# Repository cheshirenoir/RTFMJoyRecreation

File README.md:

# RTFMJoyRecreation
A recreation of the classic Acorn Archimedes joystick adaptor for use in the EcoNet module socket.
Redeveloped by the StarDot Community, including Cheshirenoir, IanJeffray, IanS, Dazzathedazza and others.
This version CC BY SA

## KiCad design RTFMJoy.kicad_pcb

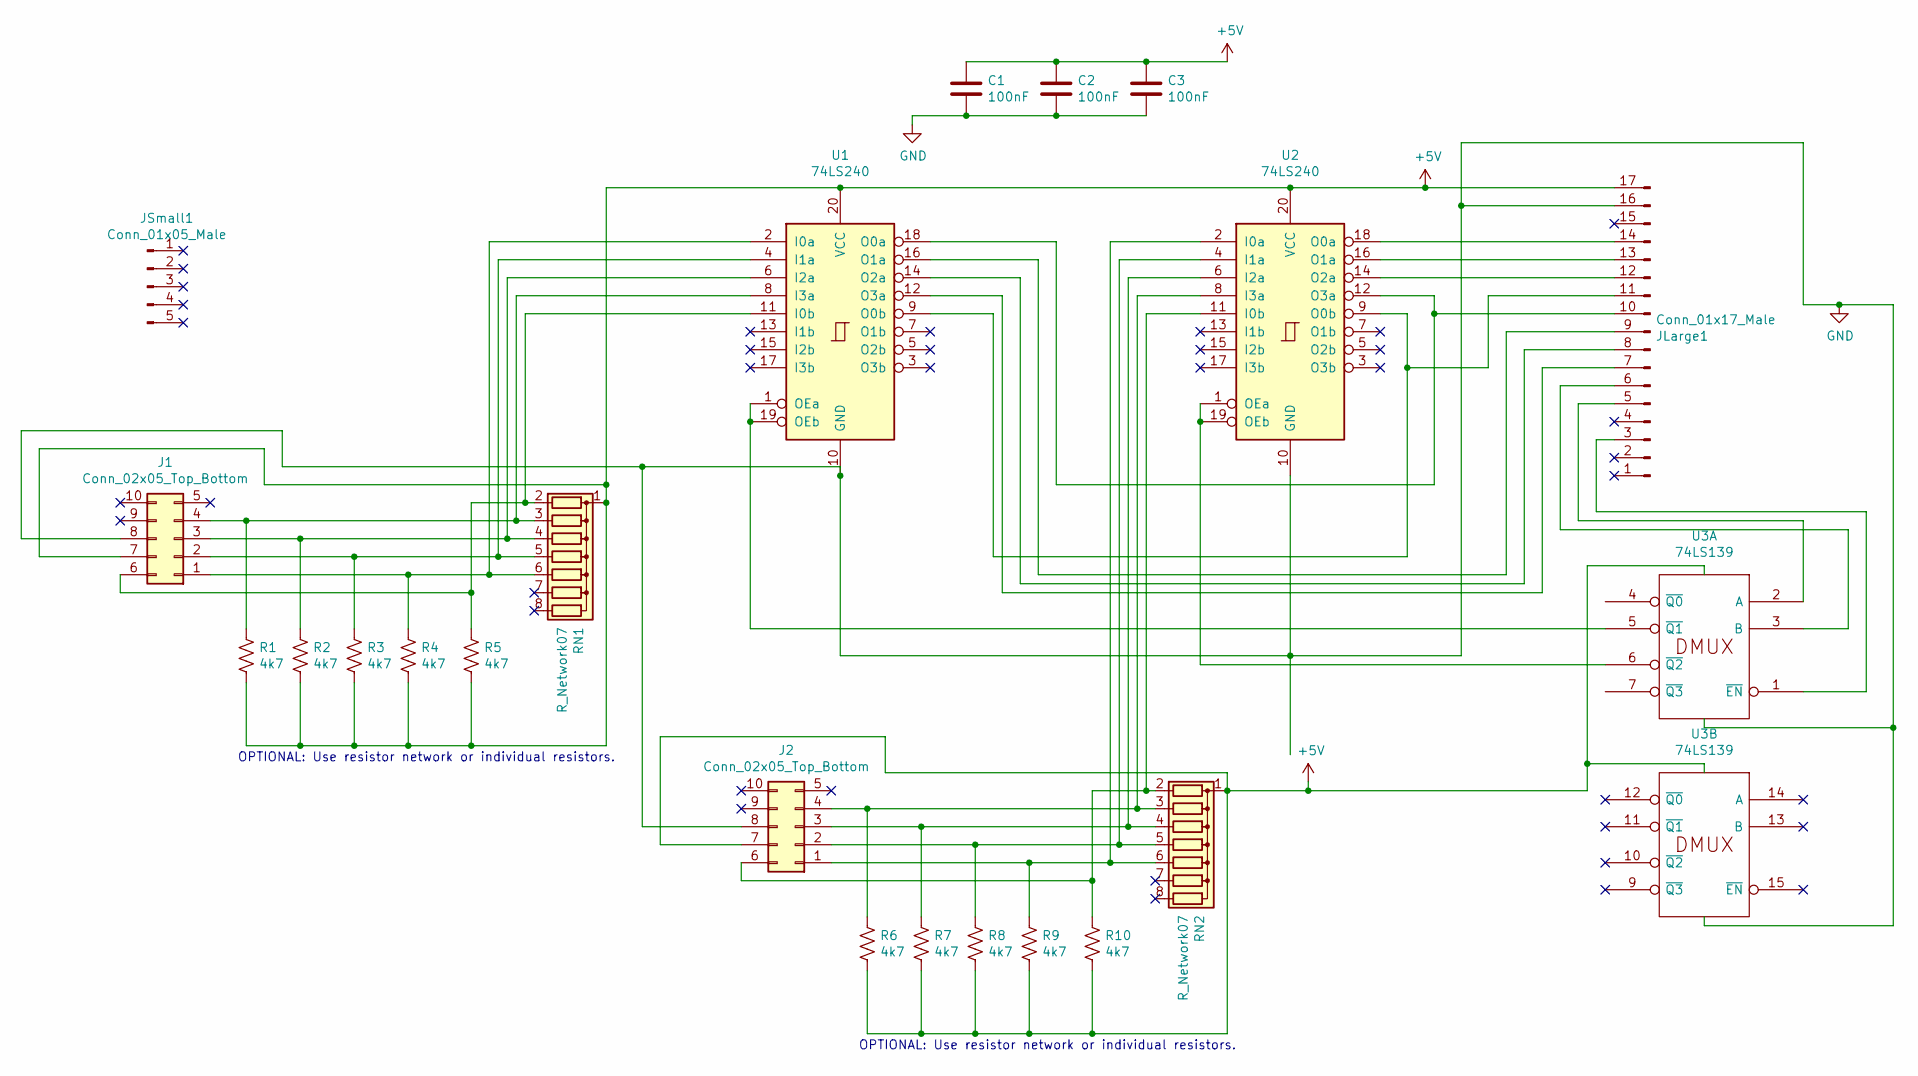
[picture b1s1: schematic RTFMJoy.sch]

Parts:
C1, C2, C3: 100nF; C_Disc_D5.0mm_W2.5mm_P5.00mm
J1, J2: Conn_02x05_Top_Bottom; IDC-Header_2x05_P2.54mm_Vertical
JLarge1: Conn_01x17_Male; PinHeader_1x17_P2.54mm_Vertical
JSmall1: Conn_01x05_Male; PinHeader_1x05_P2.54mm_Vertical
R1, R2, R3, R4, R5, R6, R7, R8, R9, R10: 4k7; R_Axial_DIN0207_L6.3mm_D2.5mm_P7.62mm_Horizontal
RN1, RN2: R_Network07; R_Array_SIP8
U1, U2: 74LS240; DIP-20_W7.62mm_Socket_LongPads
U3: 74LS139; DIP-16_W7.62mm_Socket_LongPads

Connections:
+5V: C1.1, C2.1, C3.1, J1.7, J2.7, JLarge1.17, R1.2, R2.2, R3.2, R4.2, R5.2, R6.2, R7.2, R8.2, R9.2, R10.2, RN1.1 (common), RN2.1 (common), U1.20 (VCC), U2.20 (VCC), U3.16 (VCC)
GND: C1.2, C2.2, C3.2, J1.8, J2.8, JLarge1.16, U1.10 (GND), U2.10 (GND), U3.8 (GND)
unnamed: J1.1, R4.1, RN1.6 (R5), U1.2 (I0a)
unnamed: J1.2, R3.1, RN1.5 (R4), U1.4 (I1a)
unnamed: J1.3, R2.1, RN1.4 (R3), U1.6 (I2a)
unnamed: J1.4, R1.1, RN1.3 (R2), U1.8 (I3a)
unnamed: J1.6, R5.1, RN1.2 (R1), U1.11 (I0b)
unnamed: J2.1, R9.1, RN2.6 (R5), U2.2 (I0a)
unnamed: J2.2, R8.1, RN2.5 (R4), U2.4 (I1a)
unnamed: J2.3, R7.1, RN2.4 (R3), U2.6 (I2a)
unnamed: J2.4, R6.1, RN2.3 (R2), U2.8 (I3a)
unnamed: J2.6, R10.1, RN2.2 (R1), U2.11 (I0b)
unnamed: JLarge1.3, U3.1 (~EN)
unnamed: JLarge1.5, U3.2 (A)
unnamed: JLarge1.6, U3.3 (B)
unnamed: JLarge1.7, U1.12 (O3a)
unnamed: JLarge1.8, U1.14 (O2a)
unnamed: JLarge1.9, U1.16 (O1a)
unnamed: JLarge1.10, U1.18 (O0a), U2.12 (O3a)
unnamed: JLarge1.11, U1.9 (O0b), U2.9 (O0b)
unnamed: JLarge1.12, U2.14 (O2a)
unnamed: JLarge1.13, U2.16 (O1a)
unnamed: JLarge1.14, U2.18 (O0a)
unnamed: U1.1 (OEa), U1.19 (OEb), U3.5 (~Q1)
unnamed: U2.1 (OEa), U2.19 (OEb), U3.6 (~Q2)

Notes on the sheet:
OPTIONAL: Use resistor network or individual resistors.

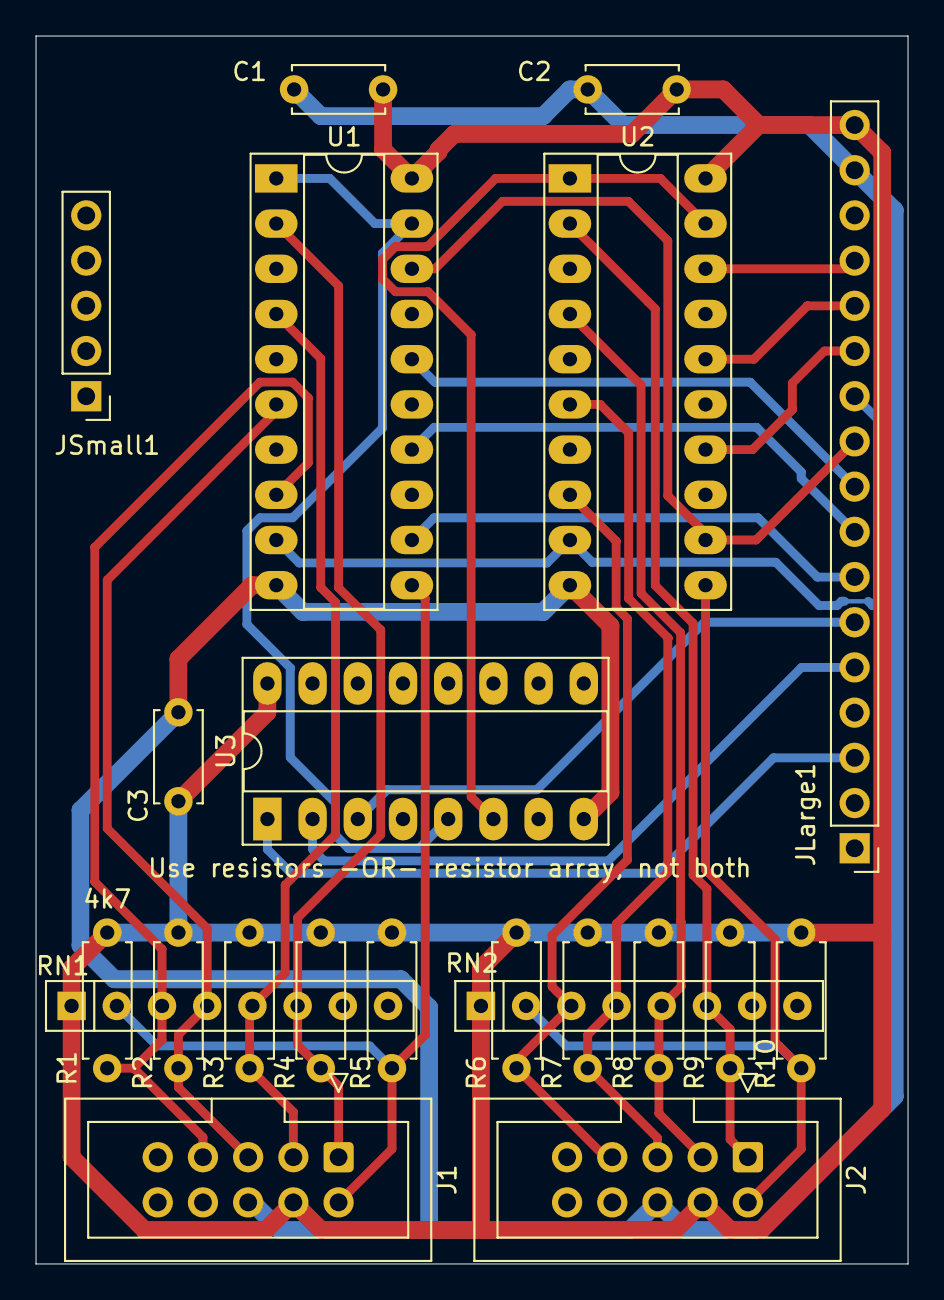
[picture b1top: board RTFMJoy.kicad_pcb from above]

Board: 2 copper layers, 49.0 x 69.0 mm, 22 parts (0 on the bottom side), 25 nets.

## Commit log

2021-06-14 Add files via upload
    Corrected an issue where the enable pins from U3 were connected to the wrong 74LS240
